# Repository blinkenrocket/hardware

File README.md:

# Hardware
This repository contains schematics, board layout and the BOM
## Expansion Headers
Blinkenrocket features expansion headers which makes un-used pins available for use. Pins are broken out on standard 2.54mm pin headers (need to be soldered on separately). VCC and GND are added for convenience. If you look at the CPU on the back the layout is as follows:

```
VCC                     VCC
E1         [CPU]         E3
E2         [CPU]         E4
GND                     GND
```

The pins map to the following pins on the microcontroller:

E1: PC0 (ADC0/PCINT8)

E2: PC1 (ADC1/PCINT9)

E3: PC2 (ADC2/PCINT10)

E4: PA1 (ADC7/PCINT25)

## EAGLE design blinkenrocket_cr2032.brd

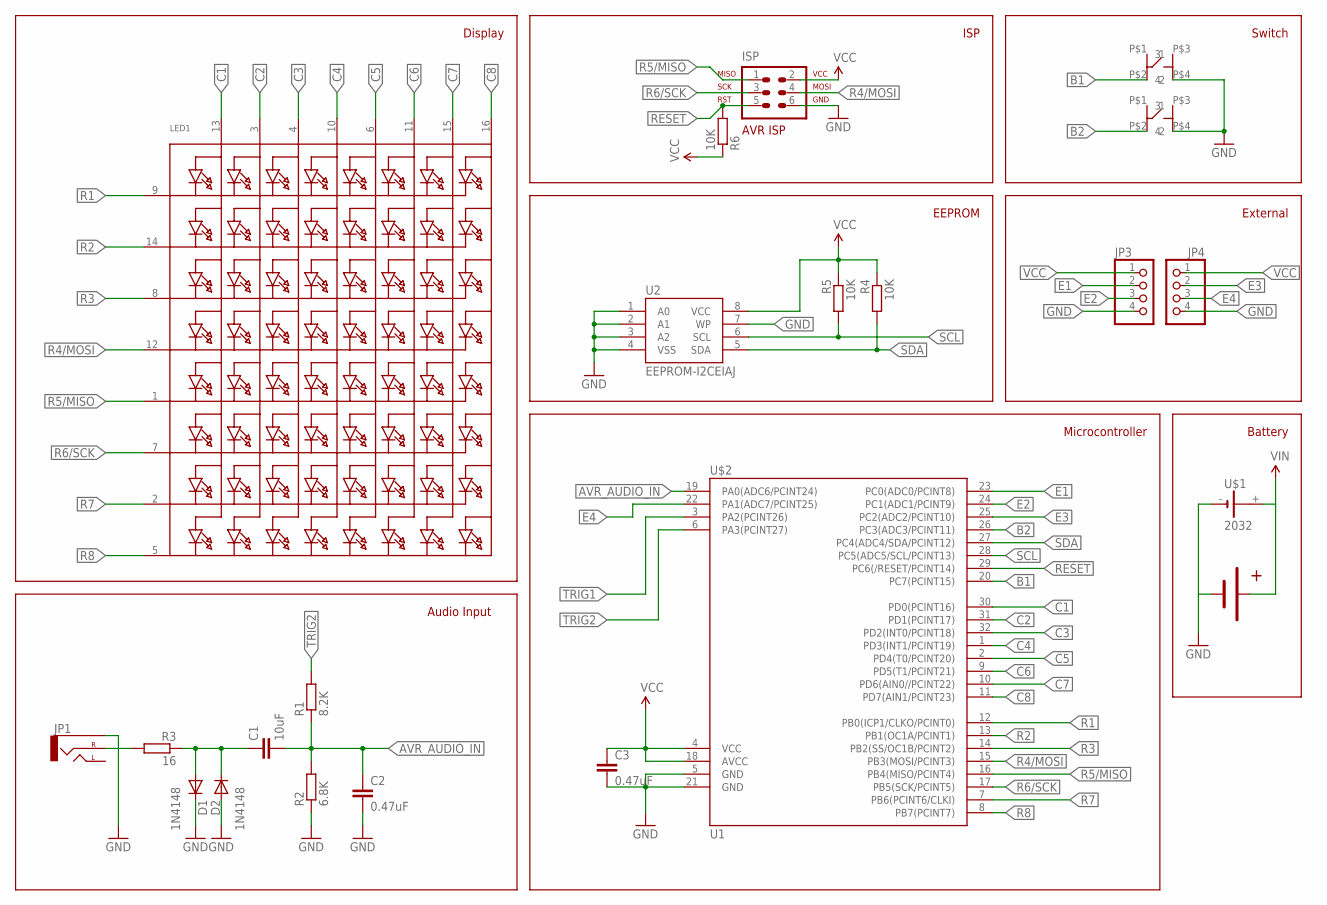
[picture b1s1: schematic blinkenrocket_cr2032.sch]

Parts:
C1: 10uF; C1206
C2, C3: 0.47uF; C1206
D1, D2: 1N4148; SOD3718X135N
ISP: AVR-ISP-6VERT; AVR-ISP-6
JP1: AUDIO-JACKPTH; AUDIO-JACK
JP3, JP4: PINHD-1X04_2.54-S; 1X04-S
LED1: SEGMENT_8X8_ROWCATHODEM12A881UR; SEGMENT_BL-M12A881UR
R1: 8.2K; R1206
R2: 6.8K; R1206
R3: 16; R1206
R4, R5, R6: 10K; R1206
SW1, SW2: SWITCH-4POMRON-6-6-SWITCH; 4P-OMRON-6-6-SWITCH
U2: EEPROM-I2CEIAJ; SO08-EIAJ
U$1: 2032; KZH20SMD
U$2: U1; TQFP32-08
U$3: BATTERYPAD

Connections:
AVR_AUDIO_IN: C1.2, C2.1, R1.1, R2.2, U$2.19 (PA0(ADC6/PCINT24))
B1: SW2.P$2 (2), U$2.20 (PC7(PCINT15))
B2: SW1.P$2 (2), U$2.26 (PC3(ADC3/PCINT11))
C1: LED1.13 (A1), U$2.30 (PD0(PCINT16))
C2: LED1.3 (A2), U$2.31 (PD1(PCINT17))
C3: LED1.4 (A3), U$2.32 (PD2(INT0/PCINT18))
C4: LED1.10 (A4), U$2.1 (PD3(INT1/PCINT19))
C5: LED1.6 (A5), U$2.2 (PD4(T0/PCINT20))
C6: LED1.11 (A6), U$2.9 (PD5(T1/PCINT21))
C7: LED1.15 (A7), U$2.10 (PD6(AIN0//PCINT22))
C8: LED1.16 (A8), U$2.11 (PD7(AIN1/PCINT23))
E1: JP3.2, U$2.23 (PC0(ADC0/PCINT8))
E2: JP3.3, U$2.24 (PC1(ADC1/PCINT9))
E3: JP4.2, U$2.25 (PC2(ADC2/PCINT10))
E4: JP4.3, U$2.22 (PA1(ADC7/PCINT25))
GND: C2.2, C3.2, D1.K, D2.A, ISP.6, JP1.SLEEVE, JP3.4, JP4.4, R2.1, SW1.P$4 (4), SW2.P$4 (4), U2.1 (A0), U2.2 (A1), U2.3 (A2), U2.4 (VSS), U2.7 (WP), U$1.-, U$2.5 (GND), U$2.21 (GND), U$3.-VE
unnamed: JP1.RING (RIGHT), R3.2
unnamed: C1.1, D1.A, D2.K, R3.1
R1: LED1.9 (K1), U$2.12 (PB0(ICP1/CLKO/PCINT0))
R2: LED1.14 (K2), U$2.13 (PB1(OC1A/PCINT1))
R3: LED1.8 (K3), U$2.14 (PB2(SS/OC1B/PCINT2))
R4/MOSI: ISP.4, LED1.12 (K4), U$2.15 (PB3(MOSI/PCINT3))
R5/MISO: ISP.1, LED1.1 (K5), U$2.16 (PB4(MISO/PCINT4))
R6/SCK: ISP.3, LED1.7 (K6), U$2.17 (PB5(SCK/PCINT5))
R7: LED1.2 (K7), U$2.7 (PB6(PCINT6/CLKI))
R8: LED1.5 (K8), U$2.8 (PB7(PCINT7))
RESET: ISP.5, R6.2, U$2.29 (PC6(/RESET/PCINT14))
SCL: R5.2, U2.6 (SCL), U$2.28 (PC5(ADC5/SCL/PCINT13))
SDA: R4.2, U2.5 (SDA), U$2.27 (PC4(ADC4/SDA/PCINT12))
TRIG1: U$2.3 (PA2(PCINT26))
TRIG2: R1.2, U$2.6 (PA3(PCINT27))
VCC: C3.1, ISP.2, JP3.1, JP4.1, R4.1, R5.1, R6.1, U2.8 (VCC), U$1.+, U$2.4 (VCC), U$2.18 (AVCC), U$3.+VE

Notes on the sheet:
Audio Input
Display
ISP
Switch
Battery
EEPROM
Microcontroller
External

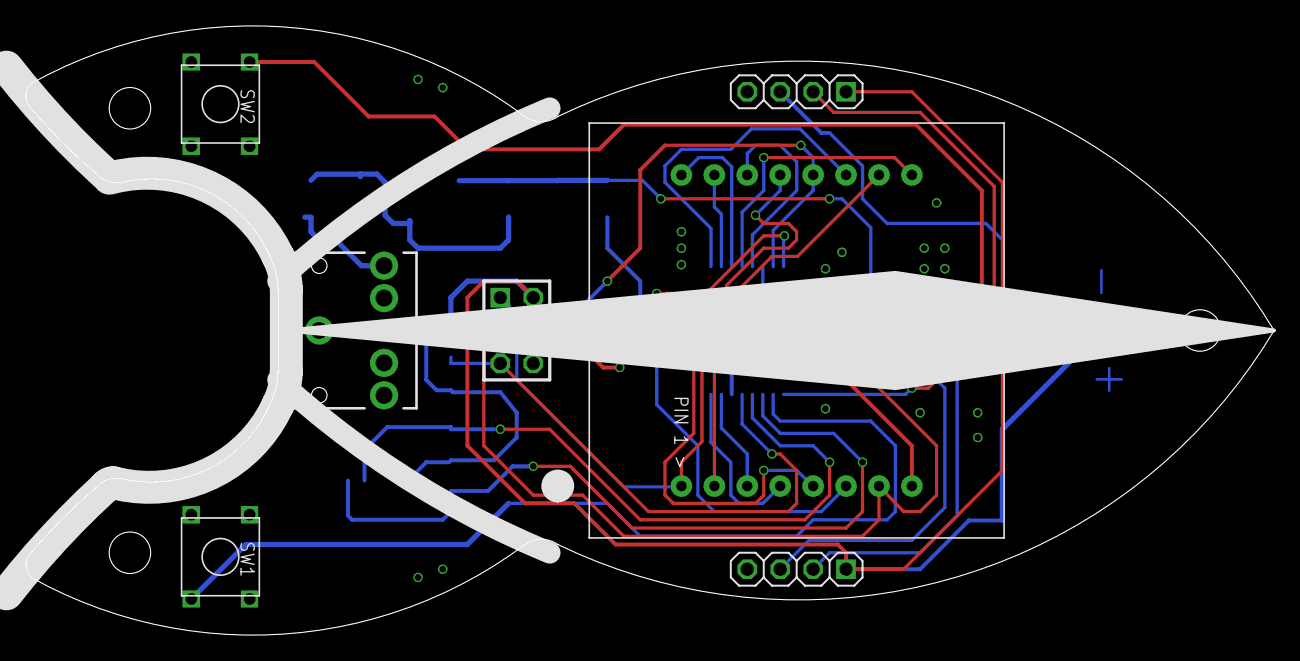
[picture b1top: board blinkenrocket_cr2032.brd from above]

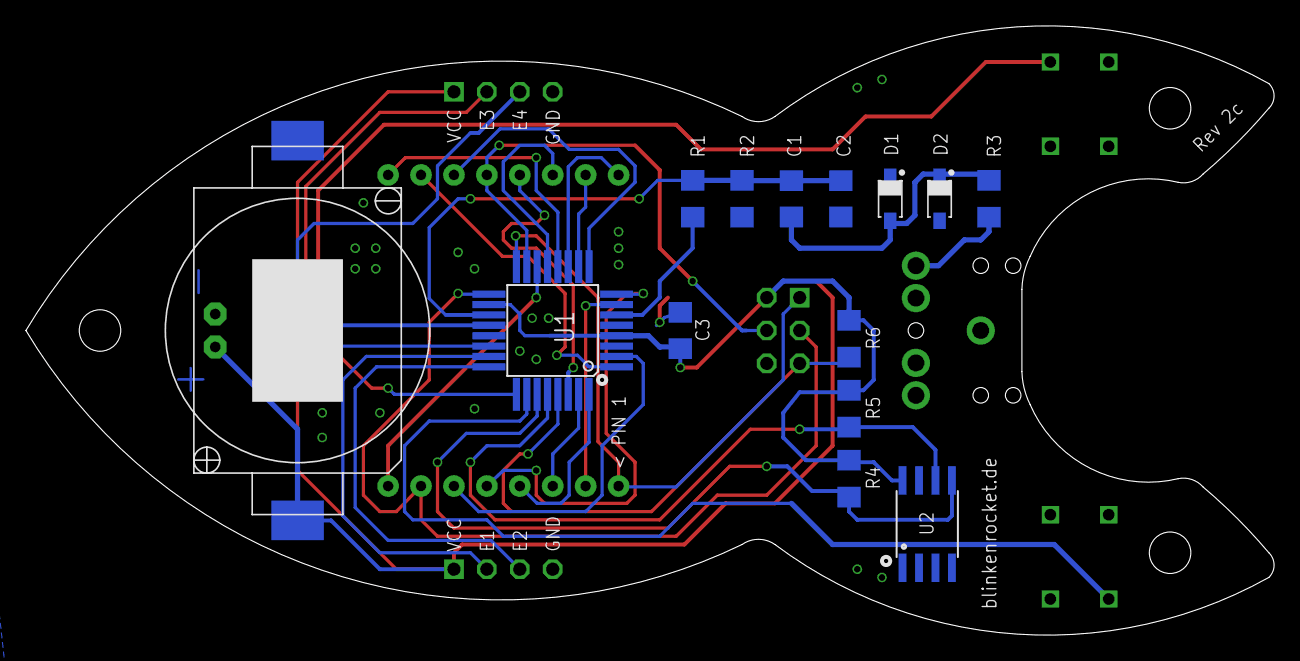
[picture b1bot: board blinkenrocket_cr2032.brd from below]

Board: 2 copper layers, 96.3 x 47.0 mm, 22 parts (15 on the bottom side), 31 nets.

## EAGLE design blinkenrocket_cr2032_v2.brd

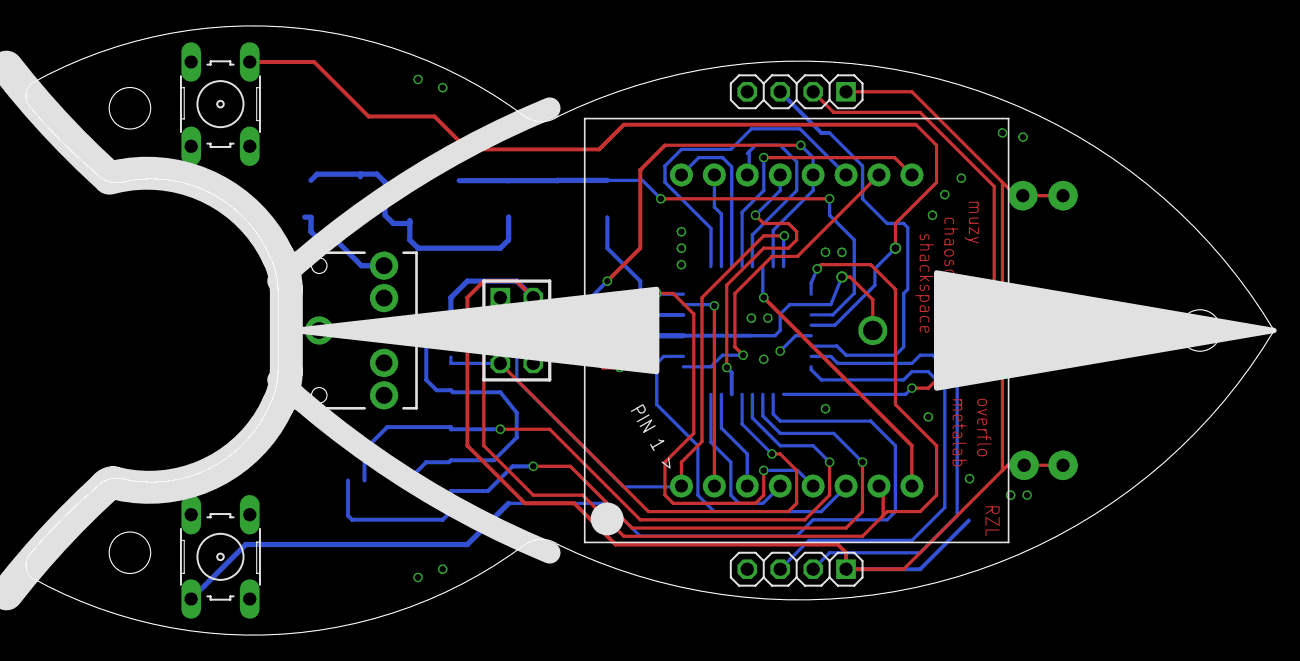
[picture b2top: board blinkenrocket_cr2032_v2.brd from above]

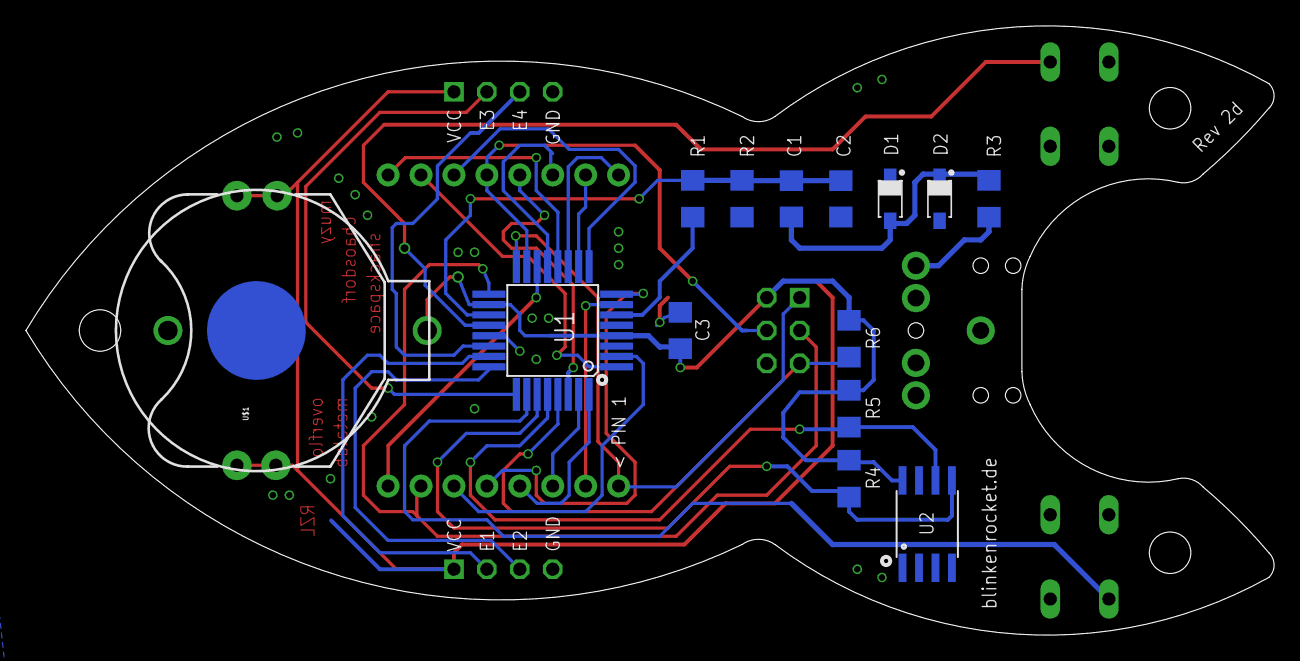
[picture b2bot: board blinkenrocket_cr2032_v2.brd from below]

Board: 2 copper layers, 96.3 x 47.0 mm, 22 parts (15 on the bottom side), 31 nets.

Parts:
C1: 10uF; C1206
C2, C3: 0.47uF; C1206
D1, D2: 1N4148; SOD3718X135N
ISP: AVR-ISP-6VERT; AVR-ISP-6
JP1: AUDIO-JACK
JP3, JP4: 1X04-S
LED2: SEGMENT_BL-M12A883
R1: 8.2K; R1206
R2: 6.8K; R1206
R3: 16; R1206
R4, R5, R6: 10K; R1206
S1, S2: B3F-10XX
U2: EEPROM-I2CEIAJ; SO08-EIAJ
U$1: LINX-BAT-HLD-001-TH; BAT_20MM_TH
U$2: U1; TQFP32-08
U$5: CR2032_ELECTRODRAGON; CR2032PAC_ELECTRODRAGON

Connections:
AVR_AUDIO_IN: C1.2, C2.1, R1.1, R2.2, U$2.19
B1: S2.1, U$2.20
B2: S1.1, U$2.26
C1: LED2.13, U$2.30
C2: LED2.3, U$2.31
C3: LED2.4, U$2.32
C4: LED2.10, U$2.1
C5: LED2.6, U$2.2
C6: LED2.11, U$2.9
C7: LED2.15, U$2.10
C8: LED2.16, U$2.11
E1: JP3.2, U$2.23
E2: JP3.3, U$2.24
E3: JP4.2, U$2.25
E4: JP4.3, U$2.22
GND: C2.2, C3.2, D1.K, D2.A, ISP.6, JP1.SLEEVE, JP3.4, JP4.4, R2.1, S1.3, S2.3, U2.1, U2.2, U2.3, U2.4, U2.7, U$1.GND, U$2.5, U$2.21, U$5.-
unnamed: JP1.RING, R3.2
unnamed: C1.1, D1.A, D2.K, R3.1
R1: LED2.9, U$2.12
R2: LED2.14, U$2.13
R3: LED2.8, U$2.14
R4/MOSI: ISP.4, LED2.12, U$2.15
R5/MISO: ISP.1, LED2.1, U$2.16
R6/SCK: ISP.3, LED2.7, U$2.17
R7: LED2.2, U$2.7
R8: LED2.5, U$2.8
RESET: ISP.5, R6.2, U$2.29
SCL: R5.2, U2.6, U$2.28
SDA: R4.2, U2.5, U$2.27
TRIG2: R1.2, U$2.6
VCC: C3.1, ISP.2, JP3.1, JP4.1, R4.1, R5.1, R6.1, U2.8, U$1.VCC1, U$1.VCC2, U$1.VCC3, U$1.VCC4, U$2.4, U$2.18, U$5.+

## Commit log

2016-01-09 Initial transfer from old repository
2016-01-15 make the powersupply of the modem part switchable by the IC for powersaving reasons
2016-01-15 add new schematic with switchable button
2016-01-16 add revision information (R2a)
2016-01-22 make the audio signal more straight to reduce the antenna effect
2016-01-22 adjusted revision tag
2016-02-12 change value of modem input resistor
2016-02-19 Revision 2c - diodes do have positioning information now - added blinkenrocket.de text - add IC component name
2016-02-19 straighten one trace
2017-12-17 Add Version 2 with different battery holder
2018-01-04 Update Readme with expansion header
2019-05-01 Add Licence

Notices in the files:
parts and their libraries:
SparkFun-DigitalIC: Licensing: Creative Commons ShareAlike 4.0 International - https://creativecommons.org/licenses/by-sa/4.0
computronics.com.au: ©Computronics Corporation Ltd, 2004
